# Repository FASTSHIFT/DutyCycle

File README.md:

# DutyCycle

**Work-Life Duty Cycle Clock / 您的工作生活时间指示器**

> *"此作品设计的最震撼之处，在于用工业语言的确定性解构了人类时间的混沌性，让一个测量电能的工具，变成了测量生命能耗的镜子。这种「硬核诗意」，正是当代批判性设计（Critical Design）的典范。" —— DeepSeek*

## 演示视频

https://www.bilibili.com/video/BV1eET1zpE64/

## 项目结构

```
DutyCycle/
├── Document/           # 文档
│   └── Commands.md     # 串口命令说明
├── Firmware/           # 固件源码
│   ├── App/            # 应用层代码
│   ├── External/       # 第三方库 (FlashDB, argparse, umm_malloc)
│   ├── Frameworks/     # 框架层 (DataBroker, DeviceManager)
│   ├── Packs/          # Keil 芯片支持包
│   └── Vendor/         # 硬件平台适配 (AT32F421)
├── Hardware/           # 硬件设计 (KiCad)
└── Tools/              # 上位机工具
    ├── WebServer/      # Web 控制台 (DutyCycle Studio)
    └── SerialUtils/    # 串口工具和驱动
```

## 快速开始

### 下载

```bash
git clone https://github.com/FASTSHIFT/DutyCycle.git --recursive
```

### 编译固件

1. 进入目录：`Firmware/Vendor/Artery/Platform/AT32F421/MDK-ARM`
2. 打开 `proj.uvprojx`，使用 Keil v5.25+ 编译

### 运行上位机

```bash
cd Tools/WebServer
pip install -r ../requirements.txt
python main.py
```

浏览器访问 http://127.0.0.1:5000

## 使用方法

### 按钮操作

| 操作 | 功能 |
|------|------|
| 关机时单击 | 开机（默认时间为固件编译时间） |
| 开机时长按 10s | 关机（指针归零） |
| 开机时单击 | 显示剩余电量 |
| 开机时双击 | 切换静音模式 |

### 时间显示

支持两种表盘模式：

**功率因数表模式 (cos-phi)**

| 刻度 | 时间 |
|------|------|
| 0.5（上） | 05:00 |
| 0.7（上） | 07:00 |
| 0.9（上） | 09:00 |
| 1.0 | 12:00 |
| 0.9（下） | 21:00 |
| 0.7（下） | 01:00 |
| 0.5（下） | 04:59 |

**线性表模式**

| 刻度 | 时间 |
|------|------|
| 0 | 00:00 |
| 12 | 12:00 |
| 24 | 23:59 |

## 系统配置

### 串口命令

通过串口终端（115200 8N1）进行配置，详见 [命令说明文档](./Document/Commands.md)。

常用命令：
- `clock -c SET -y 2025 -m 1 -d 1 -H 12 -M 0 -S 0` - 设置时间
- `alarm -c SET -i 0 -H 7 -M 30 -m 1` - 设置闹钟
- `ctrl -c SWEEP_TEST` - 指针扫动测试

### Web 控制台 (DutyCycle Studio)

提供图形化界面，支持：
- 多设备管理
- 时钟同步
- 电机控制（双通道）
- 系统监控（CPU/内存/GPU/网络上传下载速度/音频响度）
- 闹钟管理
- 音乐编曲器

## 技术规格

| 项目 | 规格 |
|------|------|
| MCU | AT32F421K8U7 (ARM Cortex-M4, 120MHz) |
| 存储 | 64KB Flash, 16KB SRAM |
| 电源 | 锂电池供电，支持 USB 充电 |
| 通信 | USB 串口 (CH341) |

## 许可证

MIT License - Copyright (c) 2024-2026 _VIFEXTech

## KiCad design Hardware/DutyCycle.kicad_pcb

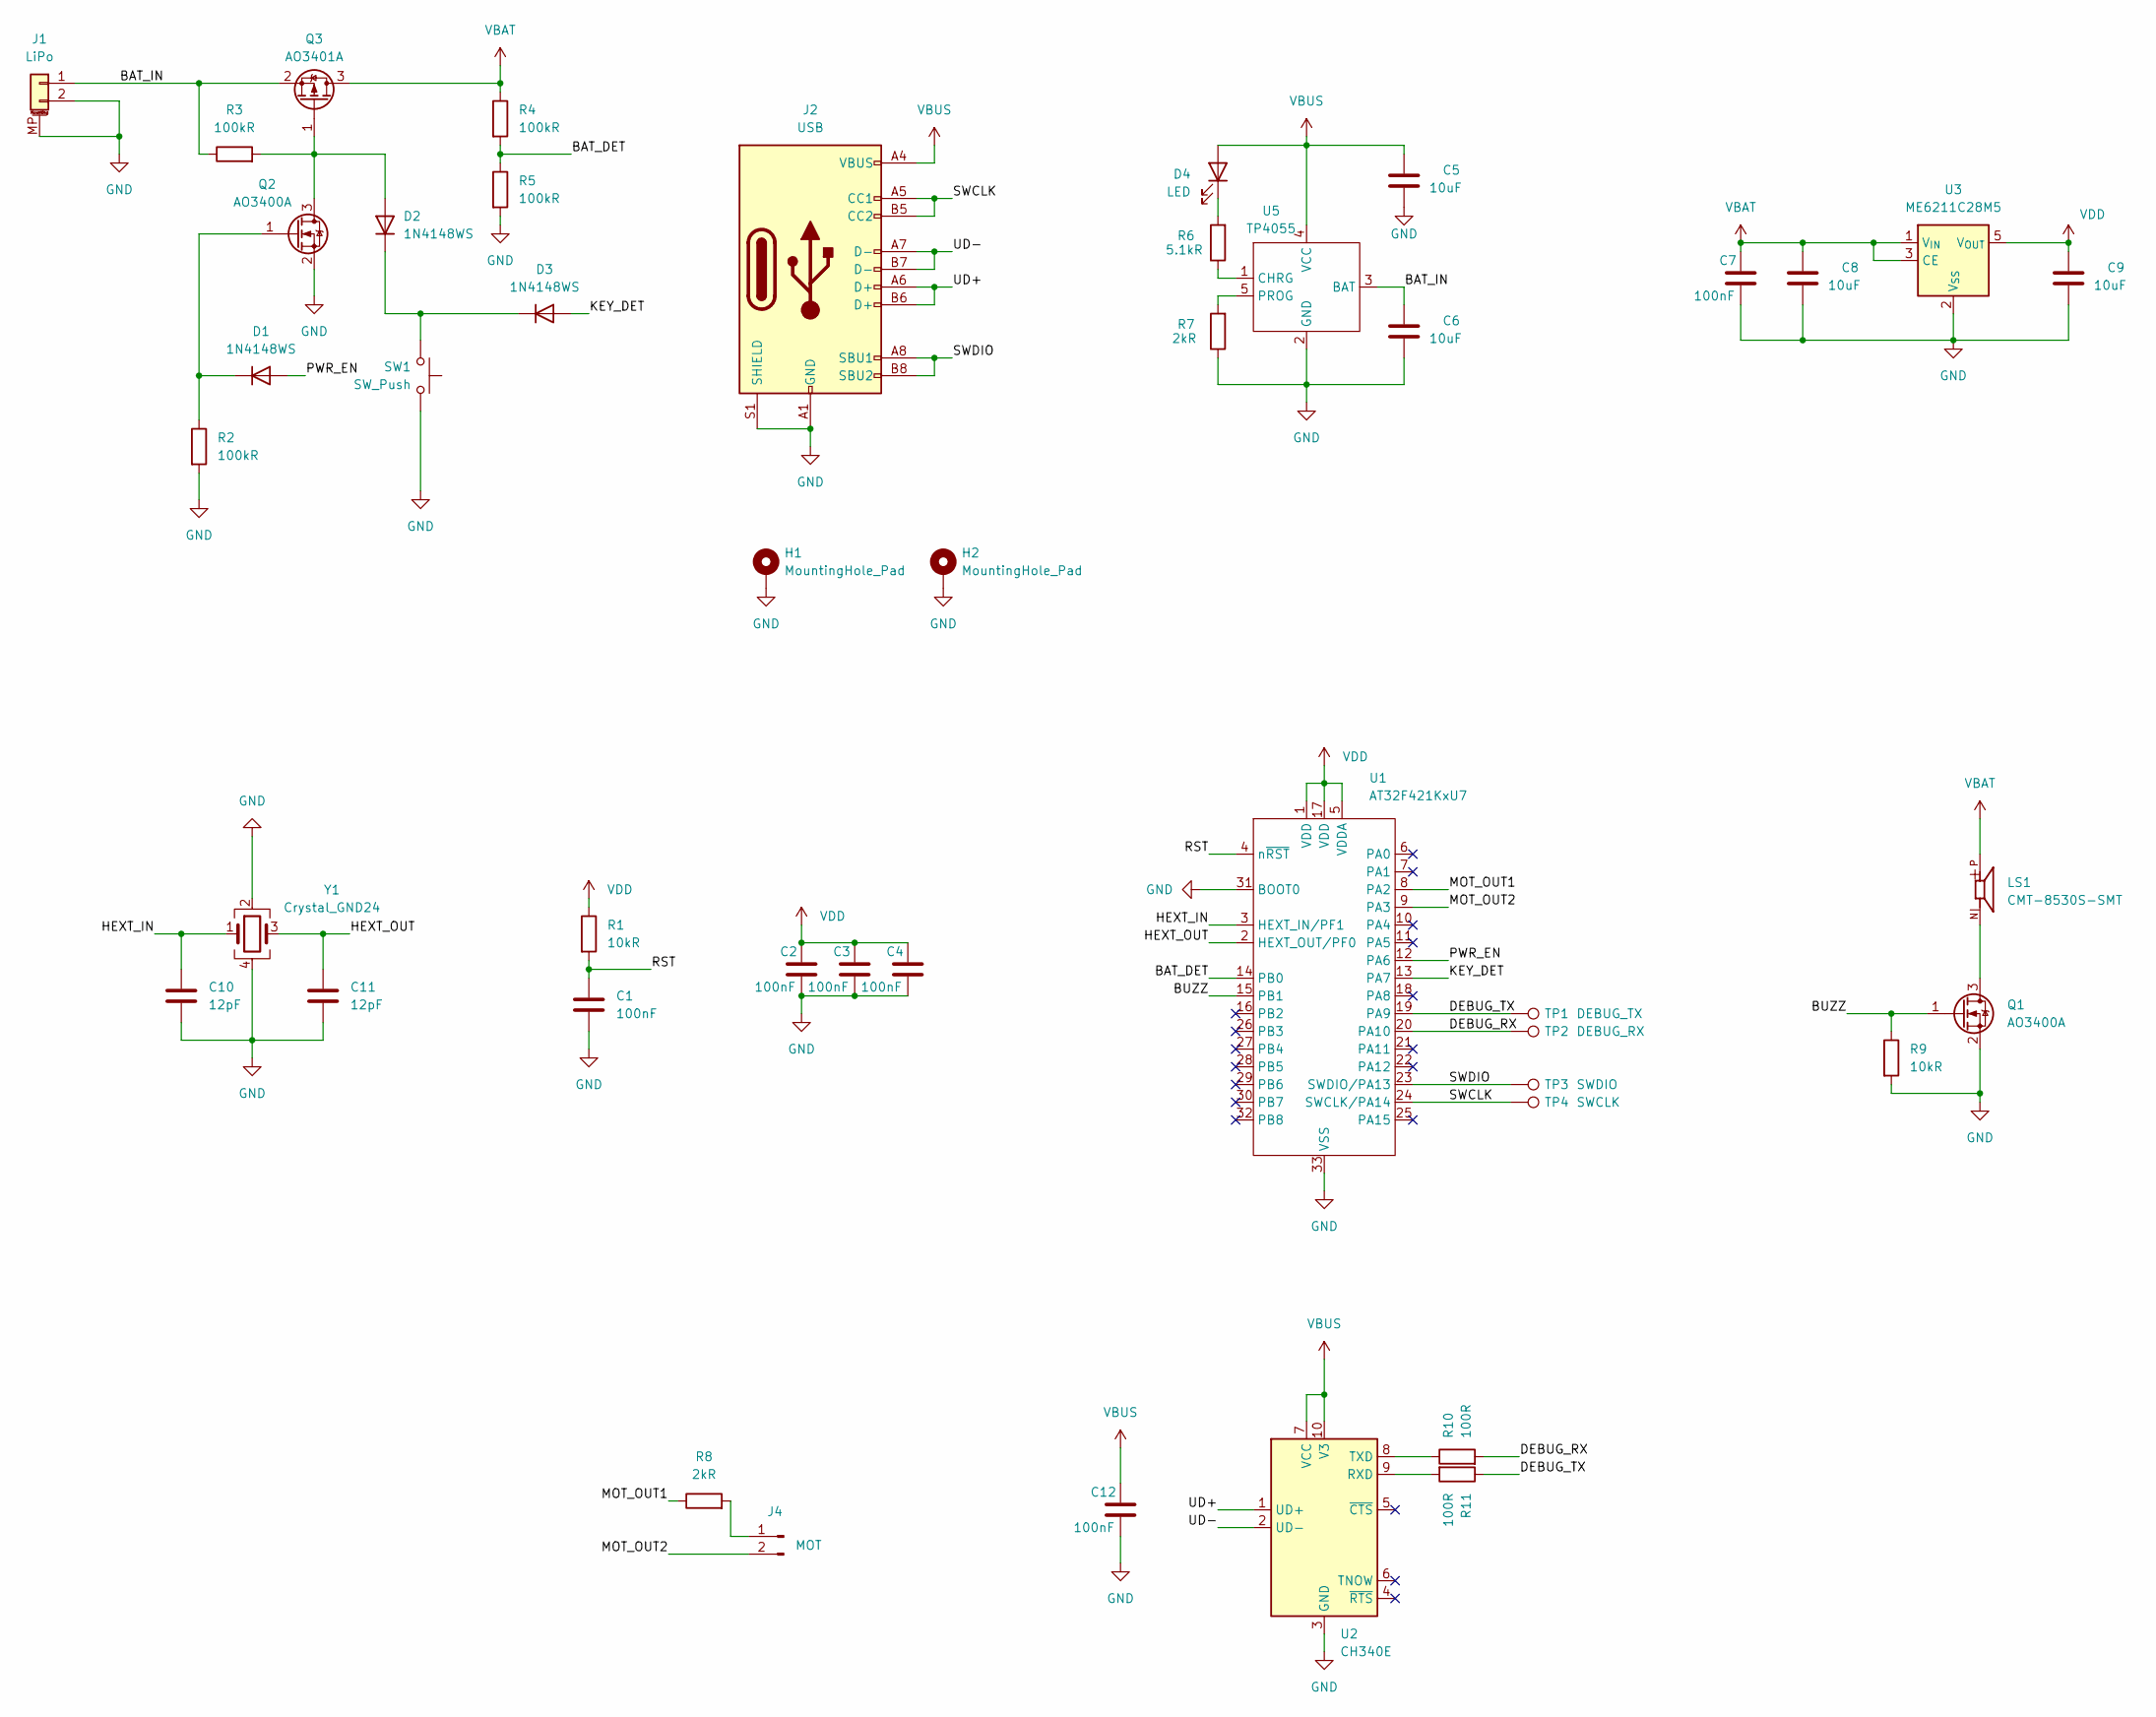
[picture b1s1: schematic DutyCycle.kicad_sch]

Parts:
C1, C2, C3, C4, C7, C12: 100nF; C_0402_1005Metric
C5, C6, C8, C9: 10uF; C_0402_1005Metric
C10, C11: 12pF; C_0402_1005Metric
D1, D2, D3: 1N4148WS; D_SOD-323
D4: LED; LED_0603_1608Metric
H1, H2: MountingHole_Pad; MountingHole_3.2mm_M3_Pad
J1: LiPo; Molex_CLIK-Mate_502494-0270_1x02-1MP_P2.00mm_Horizontal
J2: USB; USB_C_Receptacle_G-Switch_GT-USB-7051x
J4: MOT; PinHeader_1x02_P2.54mm_Vertical
LS1: CMT-8530S-SMT; CUI_CMT-8530S-SMT
Q1, Q2: AO3400A; SOT-23
Q3: AO3401A; SOT-23
R1, R9: 10kR; R_0402_1005Metric
R2, R3, R4, R5: 100kR; R_0402_1005Metric
R6: 5.1kR; R_0402_1005Metric
R7, R8: 2kR; R_0402_1005Metric
R10, R11: 100R; R_0402_1005Metric
SW1: SW_Push; SW_PUSH_6mm_H13mm
TP1: DEBUG_TX; TestPoint_Pad_D1.0mm
TP2: DEBUG_RX; TestPoint_Pad_D1.0mm
TP3: SWDIO; TestPoint_Pad_D1.0mm
TP4: SWCLK; TestPoint_Pad_D1.0mm
U1: AT32F421KxU7; QFN-32-1EP_5x5mm_P0.5mm_EP3.1x3.1mm
U2: CH340E; MSOP-10_3x3mm_P0.5mm
U3: ME6211C28M5; SOT-353_SC-70-5
U5: TP4055; SOT-23-5
Y1: Crystal_GND24; Crystal_SMD_3225-4Pin_3.2x2.5mm

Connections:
/BAT_DET: R4.2, R5.1, U1.14 (PB0)
/BAT_IN: C6.1, J1.1, Q3.2 (S), R3.1, U5.3 (BAT)
/BUZZ: Q1.1 (G), R9.1, U1.15 (PB1)
/DEBUG_RX: R10.2, TP2.1, U1.20 (PA10)
/DEBUG_TX: R11.1, TP1.1, U1.19 (PA9)
/HEXT_IN: C10.1, U1.3 (HEXT_IN/PF1), Y1.1
/HEXT_OUT: C11.1, U1.2 (HEXT_OUT/PF0), Y1.3
/KEY_DET: D3.2 (A), U1.13 (PA7)
/MOT_OUT1: R8.1, U1.8 (PA2)
/MOT_OUT2: J4.2, U1.9 (PA3)
/PWR_EN: D1.2 (A), U1.12 (PA6)
/RST: C1.1, R1.2, U1.4 (n~RST)
/SWCLK: J2.A5 (CC1), J2.B5 (CC2), TP4.1, U1.24 (SWCLK/PA14)
/SWDIO: J2.A8 (SBU1), J2.B8 (SBU2), TP3.1, U1.23 (SWDIO/PA13)
/UD+: J2.A6 (D+), J2.B6 (D+), U2.1 (UD+)
/UD-: J2.A7 (D-), J2.B7 (D-), U2.2 (UD-)
GND: C1.2, C2.2, C3.2, C4.2, C5.2, C6.2, C7.2, C8.2, C9.2, C10.2, C11.2, C12.2, H1.1, H2.1, J1.2, J1.MP (MountPin), J2.A1 (GND), J2.A12 (GND), J2.B1 (GND), J2.B12 (GND), J2.S1 (SHIELD), Q1.2 (S), Q2.2 (S), R2.2, R5.2, R7.1, R9.2, SW1.1, U1.31 (BOOT0), U1.33 (VSS), U2.3 (GND), U3.2 (V_{SS}), U5.2 (GND), Y1.2, Y1.4
unnamed: D1.1 (K), Q2.1 (G), R2.1
unnamed: D2.2 (A), Q2.3 (D), Q3.1 (G), R3.2
unnamed: D2.1 (K), D3.1 (K), SW1.2
unnamed: D4.1 (K), R6.2
unnamed: J4.1, R8.2
unnamed: LS1.N, Q1.3 (D)
unnamed: R11.2, U2.9 (RXD)
unnamed: R10.1, U2.8 (TXD)
unnamed: R6.1, U5.1 (CHRG)
unnamed: R7.2, U5.5 (PROG)
VBAT: C7.1, C8.1, LS1.P, Q3.3 (D), R4.1, U3.1 (V_{IN}), U3.3 (CE)
VBUS: C5.1, C12.1, D4.2 (A), J2.A4 (VBUS), J2.A9 (VBUS), J2.B4 (VBUS), J2.B9 (VBUS), U2.7 (VCC), U2.10 (V3), U5.4 (VCC)
VDD: C2.1, C3.1, C4.1, C9.1, R1.1, U1.1 (VDD), U1.5 (VDDA), U1.17 (VDD), U3.5 (V_{OUT})

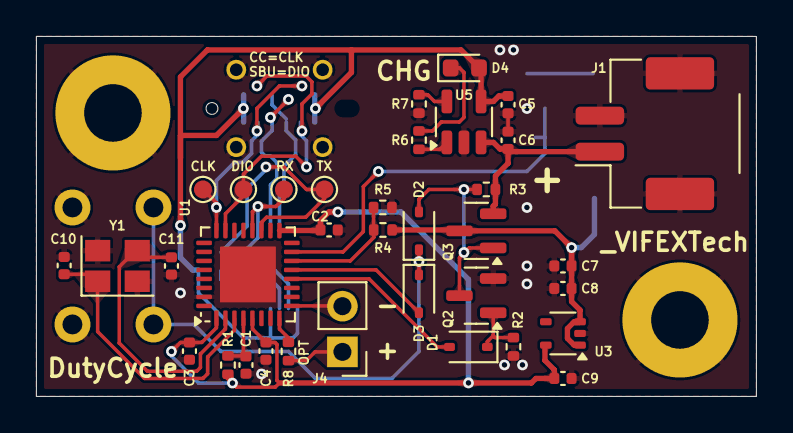
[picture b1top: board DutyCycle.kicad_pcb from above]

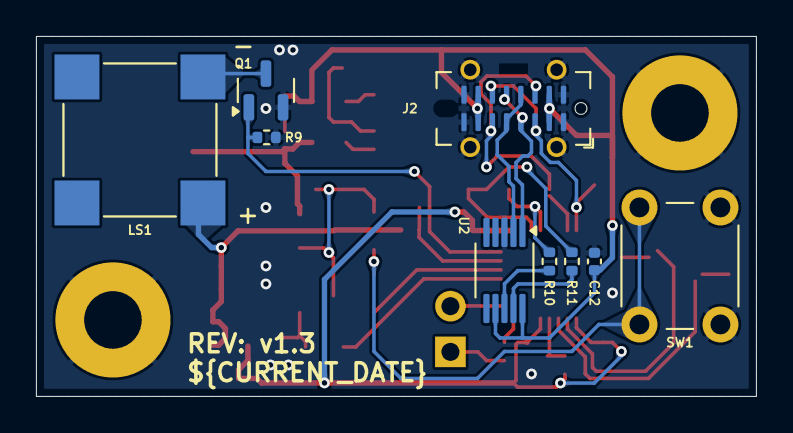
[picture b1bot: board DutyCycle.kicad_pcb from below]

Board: 2 copper layers, 40.0 x 20.0 mm, 46 parts (9 on the bottom side), 30 nets.

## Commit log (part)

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2024-12-15 feat(Hardward): upload kicad project
2024-12-15 feat(sch): rename +2.8v -> VDD
2024-12-15 feat: upload Firmware
2024-12-18 feat(pcb): finish PCB layout
2024-12-24 feat(Application): finish v1.0 firmware
2024-12-25 feat(Hardware): add external crystal & fix LDO packaging errors
2024-12-28 arch(Firmware): porting basic framework
2024-12-29 refact(ArduinoAPI): API collation and annotation
2024-12-29 fix(startup): adjust heap & stack size
2024-12-29 feat(Firmware): complete frame adaptation
2024-12-29 feat(DP_TimeMonitor): update hour filter
2024-12-30 feat(DP_TimeMonitor): adjust the tone of the timing
2024-12-30 feat(DataBroker): add timer running checker
2024-12-30 feat(DP_Power): not sleep when timeTillNext is 0
2024-12-30 feat(DataProc): add DP_Shell
2024-12-30 chore(DP_Ctrl): re-enable clock info print
2024-12-31 feat(External): add FlashDB submodule
2024-12-31 fix(flashdb_port): fix size too small
2024-12-31 chore(mcu_config): disable unused module
2024-12-31 feat(rt_sys): add fputc port
2024-12-31 feat(argparse): checkout no_exit branch
2024-12-31 feat(DP_Shell): add cmd clock
2024-12-31 chore(Shell): fix warning
2024-12-31 feat(DP_Shell): add power ctrl
2025-01-01 fix(DP_Shell): fix arg parse failed
2025-01-01 feat(DP_Audio): sound effect enhancement
2025-01-02 feat(DP_TimeMonitor): remove the back half of MC BGM
2025-01-03 feat(Audio): use constexpr to make audio sqe to RO section
2025-01-04 feat(DataBroker): support unsubscribe function to pass in pointer type
2025-01-04 feat(DP_Ctrl): complete custom hour-motor value mapping
2025-01-04 feat(DP_Power): add button long press shutdown
2025-01-05 feat(DP_Alarm): lower bpm for seq_mc_bgm
2025-01-07 feat(HAL_MemoryInfo): adding microlib adaptive
2025-01-07 feat(HAL_Battert): complete the ADC measurement of battery voltage
2025-01-08 feat(DP_Ctrl): added pointer movement speed limit
2025-01-08 feat(DP_Alarm): supports the hourly alarm filter setting independently
2025-01-08 feat(DP_Shell): add ps cmd
2025-01-12 feat(DP_Ctrl): add linear display mode support
2025-01-15 fix(DP_Shell): not display new clock week
2025-01-16 feat(DP_Audio): add mute support
2025-01-16 chore(DP_Audio): update mute log
2025-01-16 fix(startup_at32f421): expand heap size
2025-01-30 feat(Utils): add lib easing
2025-01-30 feat(DP_Ctrl): optimize memory layout and code logic
2025-01-30 chore(DP_Clock): remove alarm cmd
2025-01-31 feat(DP_Ctrl): limit pointer movement speed
2025-02-15 fix(DP_Ctrl): stop easing when set motor failed
2025-03-10 doc: add readme
2025-03-11 fix(pcb): fix silk screen errors
2025-03-15 feat(Firmware): update PIN config to adapt v1.2 hardware
2025-04-25 doc: add readme (#2)
2025-04-25 docs: update Commands doc
2025-04-25 feat(Tools): add config_clock script
2025-04-25 docs: update config_clock.py usage
2025-04-25 fix(startup_at32f421.s): adjust stack size 0x600 -> 0x640
2025-04-30 arch(Serivce): simplify global message passing
2025-04-30 feat(HAL_Log): use vprintf to reduce stack memory usage
2025-05-11 fix(Core/timer): fix irq number map error
2025-05-12 chore(config_clock): remove available_ports choices
2025-05-27 feat(Tools): add requirements.txt
2025-05-27 feat(config_clock): abstract system_monitor function
2025-05-27 feat(config_clock): add reverse mapping support
2025-05-27 feat(config_clock): add exception handle
2025-05-31 doc: update pip install requirements
2025-06-04 feat(DP_Ctrl): add LIST_CLOCK_MAP cmd
2025-06-04 doc: update ctrl & alarm cmd dsc
2025-06-05 feat(config_clock): add custom cmd file arg
2025-06-09 doc(README): update time mapping relationship table
2025-06-25 fix(DP_Audio): fix access null seq pointer
2025-06-25 feat(Version): update version info
2025-06-25 feat(gitmodules): add umm_malloc submodules
2025-06-26 fix(DP_Alarm): fix alarm music set error
2025-06-26 doc: update ararm cmd
2025-06-27 feat(HAL): add the HAL_PinRemap adaptive hardware pin
2025-06-27 feat(HAL): add HAL_MPU
2025-06-30 feat(Tools): upload Artery_ISP_Programmer & CH341 win driver
2025-07-10 docs: update dialout command
2025-07-13 feat(DP_Ctrl): add more flexible hour mappings to the linear mode
2025-07-13 chore(argparse): remove call assert()
2025-07-13 feat(MDK-ARM): switch to the AC6 compiler to reduce Flash usage
2025-07-13 fix(DP_Ctrl): fix the mismatch between _displayMode and KVDB size
2025-07-13 arch: porting cm_backtrace
2025-07-14 fix(Tools/config_clock): fix auto-config-clock default value error
2025-08-11 feat(Tools): add ubuntu desktop example
2025-10-20 feat(config_clock): add sync-clock mode
2025-10-20 fix(install_service): fix SCRIPT_PATH error
2025-12-01 feat(Tools): fix CH341SER driver restart missing
2025-12-07 feat(Clcok): add clock calibration support
2025-12-07 fix(startup_at32f421): fix stack overflow issue
    overflow stack:
    0x00000000: ?? ??:0
    0x080078ec: _fdb_write_status at ??:?
    0x08008f74: del_kv at External/FlashDB/src/fdb_kvdb.c:961
    0x0800a524: move_kv at External/FlashDB/src/fdb_kvdb.c:1015
    0x08003a78: HAL::Flash::onRead(void*, unsigned int) at DutyCycle\Firmware\Vendor\Artery\Platform\AT32F421\MDK-ARM/../../../Application/HAL/HAL_Flash.cpp:64
2026-01-01 feat(DP_Ctrl): add immediate mode control
2026-01-01 feat(clock_config): update log10 map for audio level
2026-01-02 feat(dutycycle_server): update 2x2 layout
2026-01-02 feat(dutycycle_server): add auto sync clock
2026-01-02 fix(dutycycle_server): fix the issue where the monitoring data does not update after being refreshed
2026-01-02 feat(dutycycle_server): add port check
2026-01-02 arch(Tools): reorganize the folder
2026-01-02 refact(WebServer): separate the front-end and back-end code
2026-01-02 fix(WebServer): fix the data synchronization and style issues of the checkbox
2026-01-03 feat(WebServer): supplement the component label description
2026-01-03 chore(WebServer): rename Controller -> Configuration
2026-01-03 chore(WebServer): rename Configuration -> Studio
2026-01-03 feat(WebServer): add the 'disable' style to the card
2026-01-03 feat(WebServer): add delete alarm button
2026-01-04 feat(WebServer): add CH341 scan support
2026-01-04 feat(WebServer): add alarm threshold function
2026-01-04 feat(WebServer): add cmd file monitor
2026-01-04 feat(WebServer): adaptive monitoring object list
2026-01-04 feat(install_service): support for audio monitoring in systemd
2026-01-04 chore(WebServer): remove main title emoji
2026-01-04 refact(WebServer): redesigning UI
2026-01-04 feat(WebServer): adjust card spacing
2026-01-04 chore(WebServer): adjust the emoji of the stop monitoring button
2026-01-04 feat(WebServer): optimize audio loudness mapping
2026-01-04 fix(WebServer): fix the audio display delay issue
2026-01-04 Revert "feat(WebServer): add IPv6 support"
    This reverts commit 1700ad99217d409a8544b6e27964ad14bc8e98a5.
2026-01-05 fix(WebServer): fix music arrangement preview repeating
2026-01-05 fix(WebServer): fix real-time status display was not synchronized when dragging the slider
2026-01-08 refact(WebServer): use a command queue to process serial port requests
2026-01-08 fix(WebServer): fix more than 200 lines of bu sha in the debug terminal
2026-01-08 arch(WebServer): separate event loop to worker
2026-01-08 fix(WebServer): the serial port opening and closing operations are also moved to the worker execution
2026-01-08 chore(WebServer): simplify title information
2026-01-08 fix(WebServer): ignore port usage
2026-01-18 feat(WebServer): add clock mode/hour map config
2026-02-08 feat(HAL_Motor): add dual-channel support
2026-02-08 feat(DP_Ctrl): add dual-channel independent control support
2026-02-08 ci: add CI workflow
2026-02-08 feat(DP_Ctrl): restore the dual-channel state synchronously when the key is released
2026-02-09 feat(WebServer): when ID is 0, it is not explicitly specified to maintain forward compatibility
2026-02-09 ci: add --check param
2026-02-09 test(WebServer): skip audio test for CI
2026-02-10 fix(WebServer): fix audio monitoring system that frequently fails to work
2026-02-10 docs: update README
2026-02-10 feat(WebServer): add a button to restore clock mode
2026-02-10 feat(DP_Version): add detailed information of the chip for printing
2026-02-11 test(WebServer): test framework refactoring
2026-02-11 test(WebServer): auto skip audio test
2026-02-11 test(WebServer): separate JS test cases
2026-02-11 test(WebServer): increase Python coverage to 89%
2026-02-11 fix(MotorCtrl): fix the deadlock in the logic of the 'sweepTest' animation
2026-02-11 fix(WebServer): fix the malfunction of the microphone monitoring system
2026-02-12 fix(WebServer): fix threshold alarm function not working properly
2026-02-28 feat(Tools/install_service): supports overwrite installation
2026-02-28 fix(WebServer): fix missing monitoring source configuration after reboot
2026-03-02 fix(WebServer): fix front-end audio monitoring refresh stuttering
2026-03-02 test(WebServer): configuration file isolation
2026-04-15 fix(WebServer): fix auto clock sync not working
    - Fix deadlock in check_clock_sync callback: use serial_write_direct
    instead of serial_write (which enqueue_and_wait on the same worker
    thread, causing self-deadlock and 2s timeout)
    - Fix missing setup_clock_sync_timer call in restore_state, so auto
    sync timer is created on service restart auto-reconnect
    - Add frontend polling (60s) to refresh last sync time display after
2026-04-15 chore(deps-dev): bump picomatch in /Tools/WebServer/tests/js
    Bumps [picomatch](https://github.com/micromatch/picomatch) from 2.3.1 to 2.3.2.
    - [Release notes](https://github.com/micromatch/picomatch/releases)
    - [Changelog](https://github.com/micromatch/picomatch/blob/master/CHANGELOG.md)
    - [Commits](https://github.com/micromatch/picomatch/compare/2.3.1...2.3.2)
    ---
    updated-dependencies:
2026-04-15 chore(deps): bump @tootallnate/once and jest-environment-jsdom
    Removes [@tootallnate/once](https://github.com/TooTallNate/once). It's no longer used after updating ancestor dependency [jest-environment-jsdom](https://github.com/jestjs/jest/tree/HEAD/packages/jes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
    Removes `@tootallnate/once`
    Updates `jest-environment-jsdom` from 29.7.0 to 30.3.0
    - [Release notes](https://github.com/jestjs/jest/releases)
    - [Changelog](https://github.com/jestjs/jest/blob/main/CHANGELOG.md)
    - [Commits](https://github.com/jestjs/jest/commits/v30.3.0/packages/jest-environment-jsdom)
2026-05-10 feat(Clock): support configurable RTC poll period via shell
2026-05-11 chore(deps-dev): bump @babel/plugin-transform-modules-systemjs (#6)
    Bumps [@babel/plugin-transform-modules-systemjs](https://github.com/babel/babel/tree/HEAD/packages/babel-plugin-transform-modules-systemjs) from 7.29.0 to 7.29.4.
    - [Release notes](https://github.com/babel/babel/releases)
    - [Changelog](https://github.com/babel/babel/blob/main/CHANGELOG.md)
    - [Commits](https://github.com/babel/babel/commits/v7.29.4/packages/babel-plugin-transform-modules-systemjs)
    ---
    updated-dependencies:
2026-05-16 refactor(easing): rewrite with Q1.15 fixed-point, eliminate float dependency
    - Replace float easing_pos_t with int32_t (direct integer position)
    - Internal progress uses Q1.15 format (0~32768 = 0.0~1.0)
    - All polynomial curves (Linear/Quad/Cubic/Quart/Quint/Back) use pure
    integer arithmetic, no float operations
    - Rename API to snake_case style (easing_calc_in_out_quad, etc.)
    - Remove Sine/Elastic/Expo/Circ curves (require trig functions)
2026-05-16 chore(deps): switch umm_malloc to FASTSHIFT/no-float branch
    Replace sqrtf in umm_info.c with integer sqrt to eliminate the last
    float dependency from the firmware.
2026-05-16 ci: add firmware build workflow with float-free verification
    - Build AT32F421 firmware using arm-none-eabi-gcc on Ubuntu
    - Export .hex/.bin/.elf as downloadable artifacts
    - check_float.sh verifies zero floating-point symbols in binary
    - Triggered on Firmware/** changes or manual dispatch
2026-05-16 refactor(DP_Clock): replace sscanf with manual parsing of __DATE__/__TIME__
    Eliminates sscanf dependency, saving ~3KB of C library code.
    __DATE__ and __TIME__ have fixed formats, trivial to parse manually.
    Flash: 62,200B -> 59,140B (-3,060B)
2026-05-16 docs: add log system optimization plan
    Analyze logging overhead (~16.5KB, 28% of flash):
    - printf engine: 6.4KB
    - format strings: ~6KB
    - __func__ names: ~4KB (201 strings)
    Propose 3 optimization levels as reserve for future space pressure.

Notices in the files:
README.md:
License: MIT
